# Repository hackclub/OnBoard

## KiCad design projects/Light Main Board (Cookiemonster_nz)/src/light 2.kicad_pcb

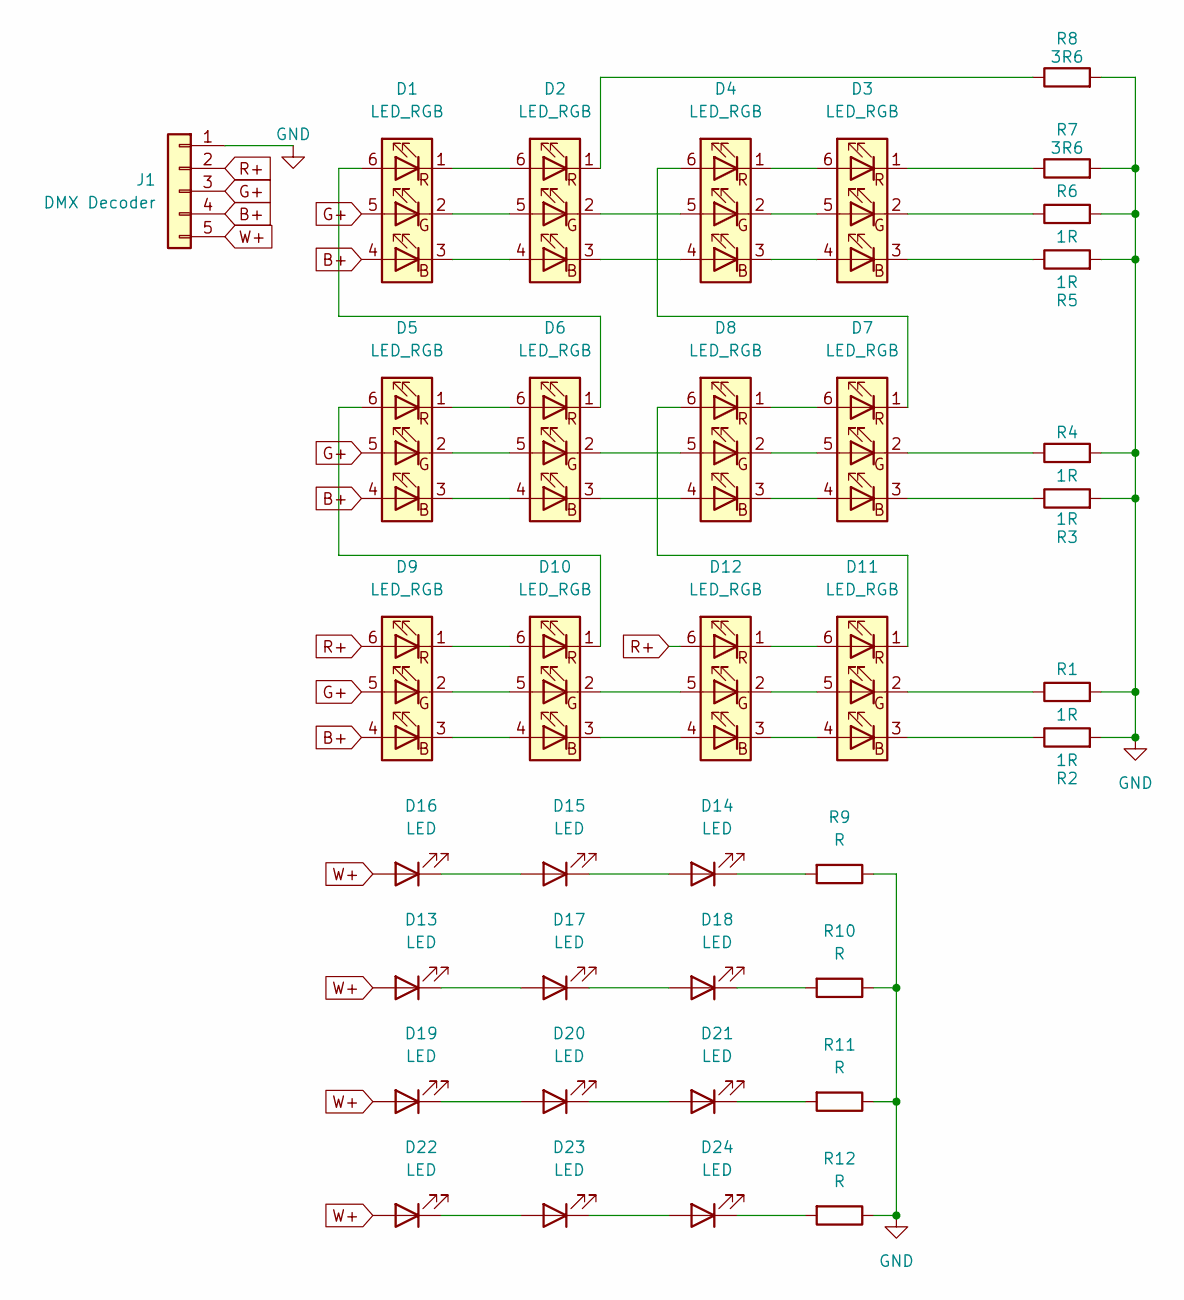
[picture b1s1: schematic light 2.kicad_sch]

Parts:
D1, D2, D3, D4, D5, D6, D7, D8, D9, D10, D11, D12: LED_RGB; RGB LED
D13, D14, D15, D16, D17, D18, D19, D20, D21, D22, D23, D24: LED; White Led Aliexpress ones
J1: DMX Decoder; 5 pin connector
R1, R2, R3, R4, R5, R6: 1R; R_1210_3225Metric
R7, R8: 3R6; R_1210_3225Metric
R9, R10, R11, R12: R; R_1210_3225Metric

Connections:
B+: D1.4 (BA), D5.4 (BA), D9.4 (BA), J1.4 (CH3)
G+: D1.5 (GA), D5.5 (GA), D9.5 (GA), J1.3 (CH2)
GND: J1.1 (COM), R1.2, R2.2, R3.2, R4.2, R5.2, R6.2, R7.2, R8.2, R9.1, R10.1, R11.1, R12.1
unnamed: D1.3 (BK), D2.4 (BA)
unnamed: D1.2 (GK), D2.5 (GA)
unnamed: D1.6 (RA), D6.1 (RK)
unnamed: D1.1 (RK), D2.6 (RA)
unnamed: D2.3 (BK), D4.4 (BA)
unnamed: D2.2 (GK), D4.5 (GA)
unnamed: D2.1 (RK), R8.1
unnamed: D3.4 (BA), D4.3 (BK)
unnamed: D3.3 (BK), R5.1
unnamed: D3.5 (GA), D4.2 (GK)
unnamed: D3.2 (GK), R6.1
unnamed: D3.6 (RA), D4.1 (RK)
unnamed: D3.1 (RK), R7.1
unnamed: D4.6 (RA), D7.1 (RK)
unnamed: D5.3 (BK), D6.4 (BA)
unnamed: D5.2 (GK), D6.5 (GA)
unnamed: D5.1 (RK), D6.6 (RA)
unnamed: D6.3 (BK), D8.4 (BA)
unnamed: D6.2 (GK), D8.5 (GA)
unnamed: D7.4 (BA), D8.3 (BK)
unnamed: D7.3 (BK), R3.1
unnamed: D7.5 (GA), D8.2 (GK)
unnamed: D7.2 (GK), R4.1
unnamed: D7.6 (RA), D8.1 (RK)
unnamed: D9.3 (BK), D10.4 (BA)
unnamed: D10.3 (BK), D12.4 (BA)
unnamed: D9.2 (GK), D10.5 (GA)
unnamed: D10.2 (GK), D12.5 (GA)
unnamed: D9.1 (RK), D10.6 (RA)
unnamed: D5.6 (RA), D10.1 (RK)
unnamed: D11.4 (BA), D12.3 (BK)
unnamed: D11.3 (BK), R2.1
unnamed: D11.5 (GA), D12.2 (GK)
unnamed: D11.2 (GK), R1.1
unnamed: D11.6 (RA), D12.1 (RK)
unnamed: D8.6 (RA), D11.1 (RK)
unnamed: D13.1 (K), D17.2 (A)
unnamed: D14.2 (A), D15.1 (K)
unnamed: D14.1 (K), R9.2
unnamed: D15.2 (A), D16.1 (K)
unnamed: D17.1 (K), D18.2 (A)
unnamed: D18.1 (K), R10.2
unnamed: D19.1 (K), D20.2 (A)
unnamed: D20.1 (K), D21.2 (A)
unnamed: D21.1 (K), R11.2
unnamed: D22.1 (K), D23.2 (A)
unnamed: D23.1 (K), D24.2 (A)
unnamed: D24.1 (K), R12.2
R+: D9.6 (RA), D12.6 (RA), J1.2 (CH1)
W+: D13.2 (A), D16.2 (A), D19.2 (A), D22.2 (A), J1.5 (CH4)

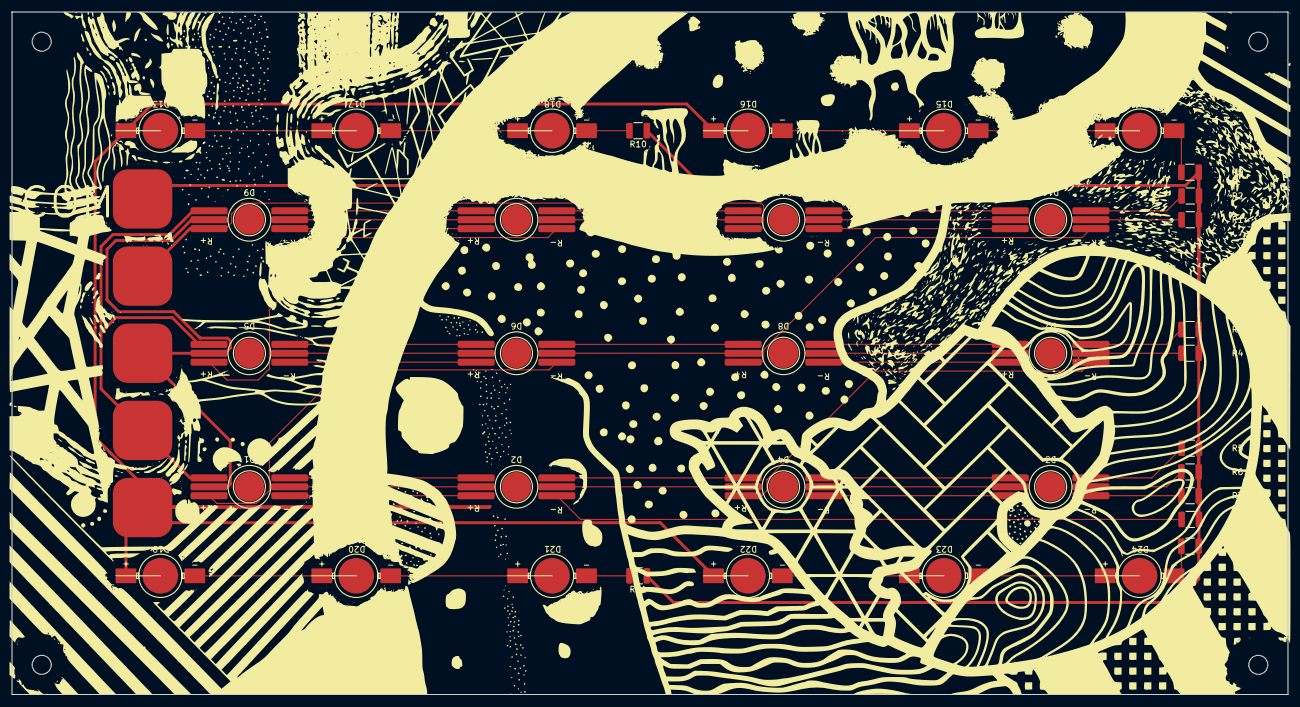
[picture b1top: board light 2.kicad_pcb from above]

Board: 2 copper layers, 215.0 x 115.0 mm, 37 parts (0 on the bottom side), 53 nets.

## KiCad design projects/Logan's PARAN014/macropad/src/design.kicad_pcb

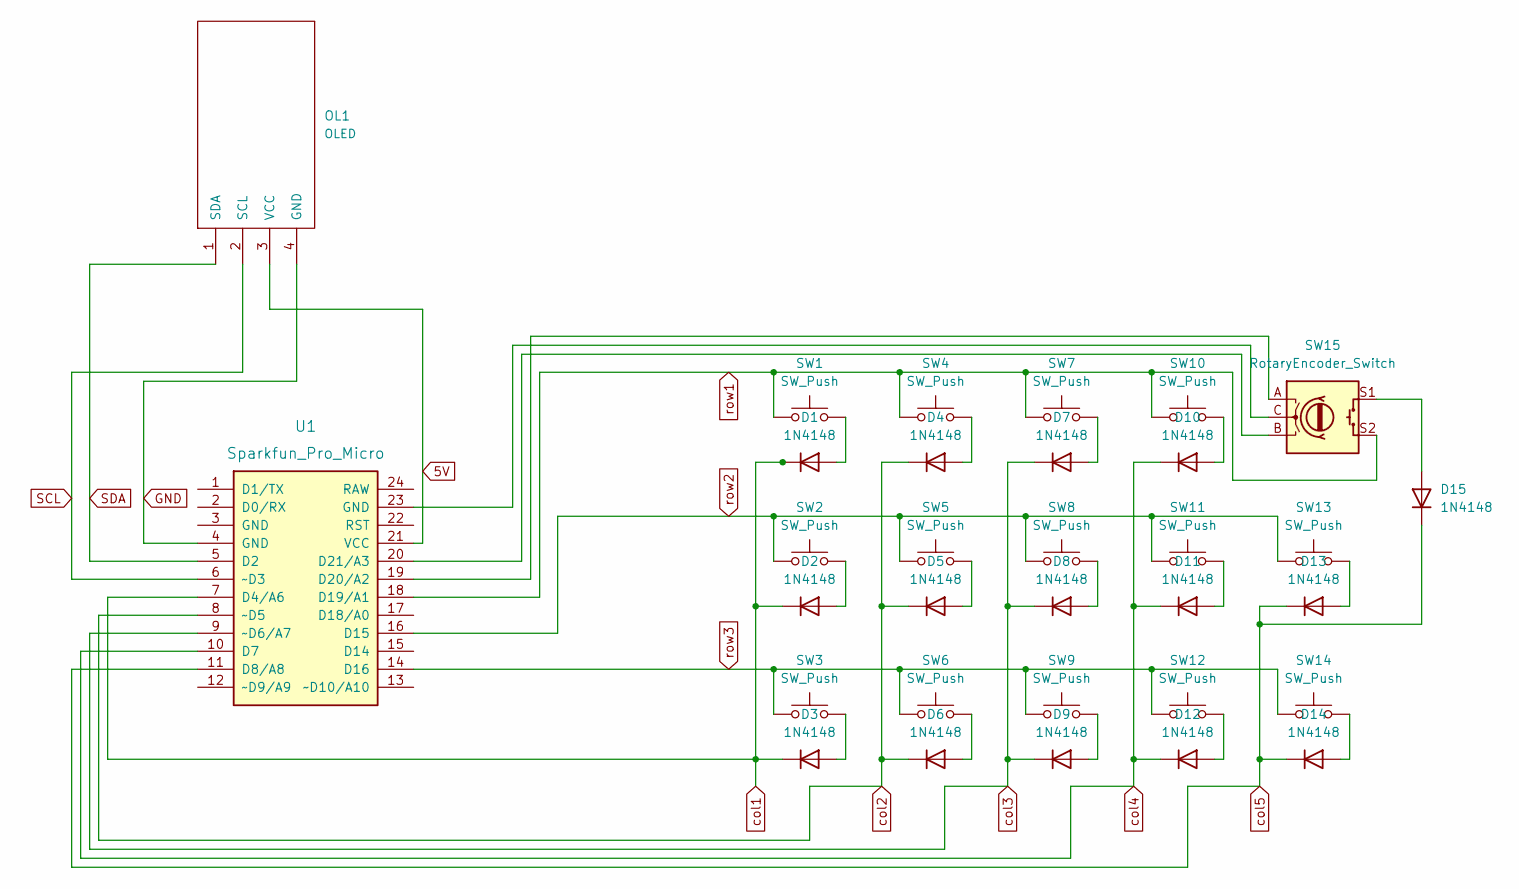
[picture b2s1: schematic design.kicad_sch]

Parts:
D1, D2, D3, D4, D5, D6, D7, D8, D9, D10, D11, D12, D13, D14, D15: 1N4148; D_DO-35_SOD27_P7.62mm_Horizontal
OL1: OLED; OLED_v2
SW1, SW2, SW3, SW4, SW5, SW6, SW7, SW8, SW9, SW10, SW11, SW12, SW13, SW14: SW_Push; SW_Cherry_MX_1.00u_PCB
SW15: RotaryEncoder_Switch; RotaryEncoder_Alps_EC11E-Switch_Vertical_H20mm
U1: Sparkfun_Pro_Micro

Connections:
5V: OL1.3 (VCC), U1.21 (VCC)
GND: OL1.4 (GND), U1.4 (GND)
unnamed: D1.2 (A), SW1.2
unnamed: D2.2 (A), SW2.2
unnamed: D3.2 (A), SW3.2
unnamed: D4.2 (A), SW4.2
unnamed: D5.2 (A), SW5.2
unnamed: D6.2 (A), SW6.2
unnamed: D7.2 (A), SW7.2
unnamed: D8.2 (A), SW8.2
unnamed: D9.2 (A), SW9.2
unnamed: D10.2 (A), SW10.2
unnamed: D11.2 (A), SW11.2
unnamed: D12.2 (A), SW12.2
unnamed: D13.2 (A), SW13.2
unnamed: D14.2 (A), SW14.2
unnamed: D15.2 (A), SW15.S1
unnamed: SW15.A, U1.19 (D20/A2)
unnamed: SW15.B, U1.20 (D21/A3)
unnamed: SW15.C, U1.23 (GND)
SCL: OL1.2 (SCL), U1.6 (~D3)
SDA: OL1.1 (SDA), U1.5 (D2)
col1: D1.1 (K), D2.1 (K), D3.1 (K), U1.7 (D4/A6)
col2: D4.1 (K), D5.1 (K), D6.1 (K), U1.8 (~D5)
col3: D7.1 (K), D8.1 (K), D9.1 (K), U1.9 (~D6/A7)
col4: D10.1 (K), D11.1 (K), D12.1 (K), U1.10 (D7)
col5: D13.1 (K), D14.1 (K), D15.1 (K), U1.11 (D8/A8)
row1: SW1.1, SW4.1, SW7.1, SW10.1, SW15.S2, U1.18 (D19/A1)
row2: SW2.1, SW5.1, SW8.1, SW11.1, SW13.1, U1.16 (D15)
row3: SW3.1, SW6.1, SW9.1, SW12.1, SW14.1, U1.14 (D16)

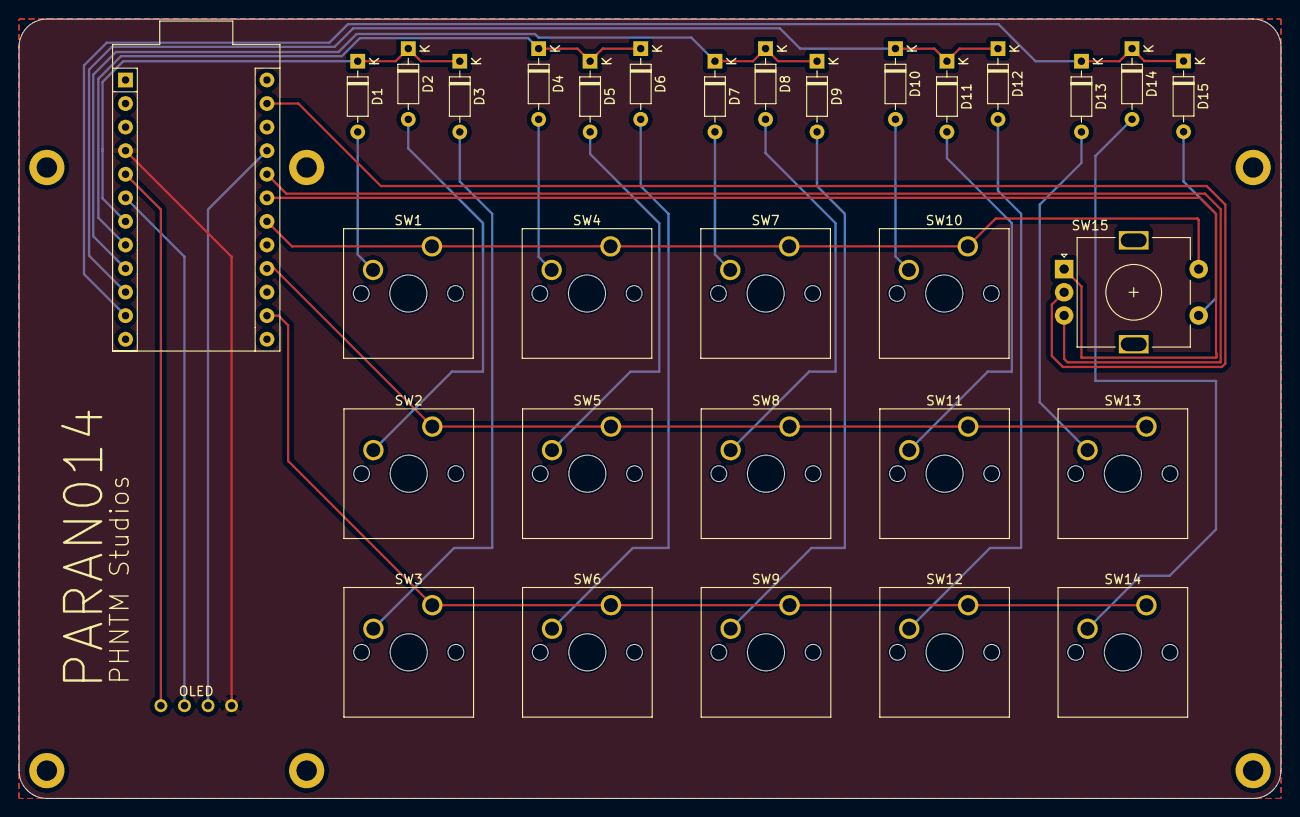
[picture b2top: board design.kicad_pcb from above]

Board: 2 copper layers, 136.0 x 84.0 mm, 32 parts (0 on the bottom side), 30 nets.

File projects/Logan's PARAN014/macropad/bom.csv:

"Id";"Designator";"Footprint";"Quantity";"Designation";"Supplier and ref";
1;"D14,D2,D3,D6,D5,D8,D15,D13,D11,D10,D7,D1,D4,D12,D9";"D_DO-35_SOD27_P7.62mm_Horizontal";15;"1N4148";;;
2;"SW9,SW5,SW3,SW1,SW7,SW13,SW4,SW11,SW10,SW14,SW12,SW6,SW2,SW8";"SW_Cherry_MX_1.00u_PCB";14;"SW_Push";;;
3;"SW15";"RotaryEncoder_Alps_EC11E-Switch_Vertical_H20mm";1;"RotaryEncoder_Switch";;;
4;"U1";"Sparkfun_Pro_Micro";1;"Sparkfun_Pro_Micro";;;
5;"OL1";"OLED_v2";1;"OLED";;;

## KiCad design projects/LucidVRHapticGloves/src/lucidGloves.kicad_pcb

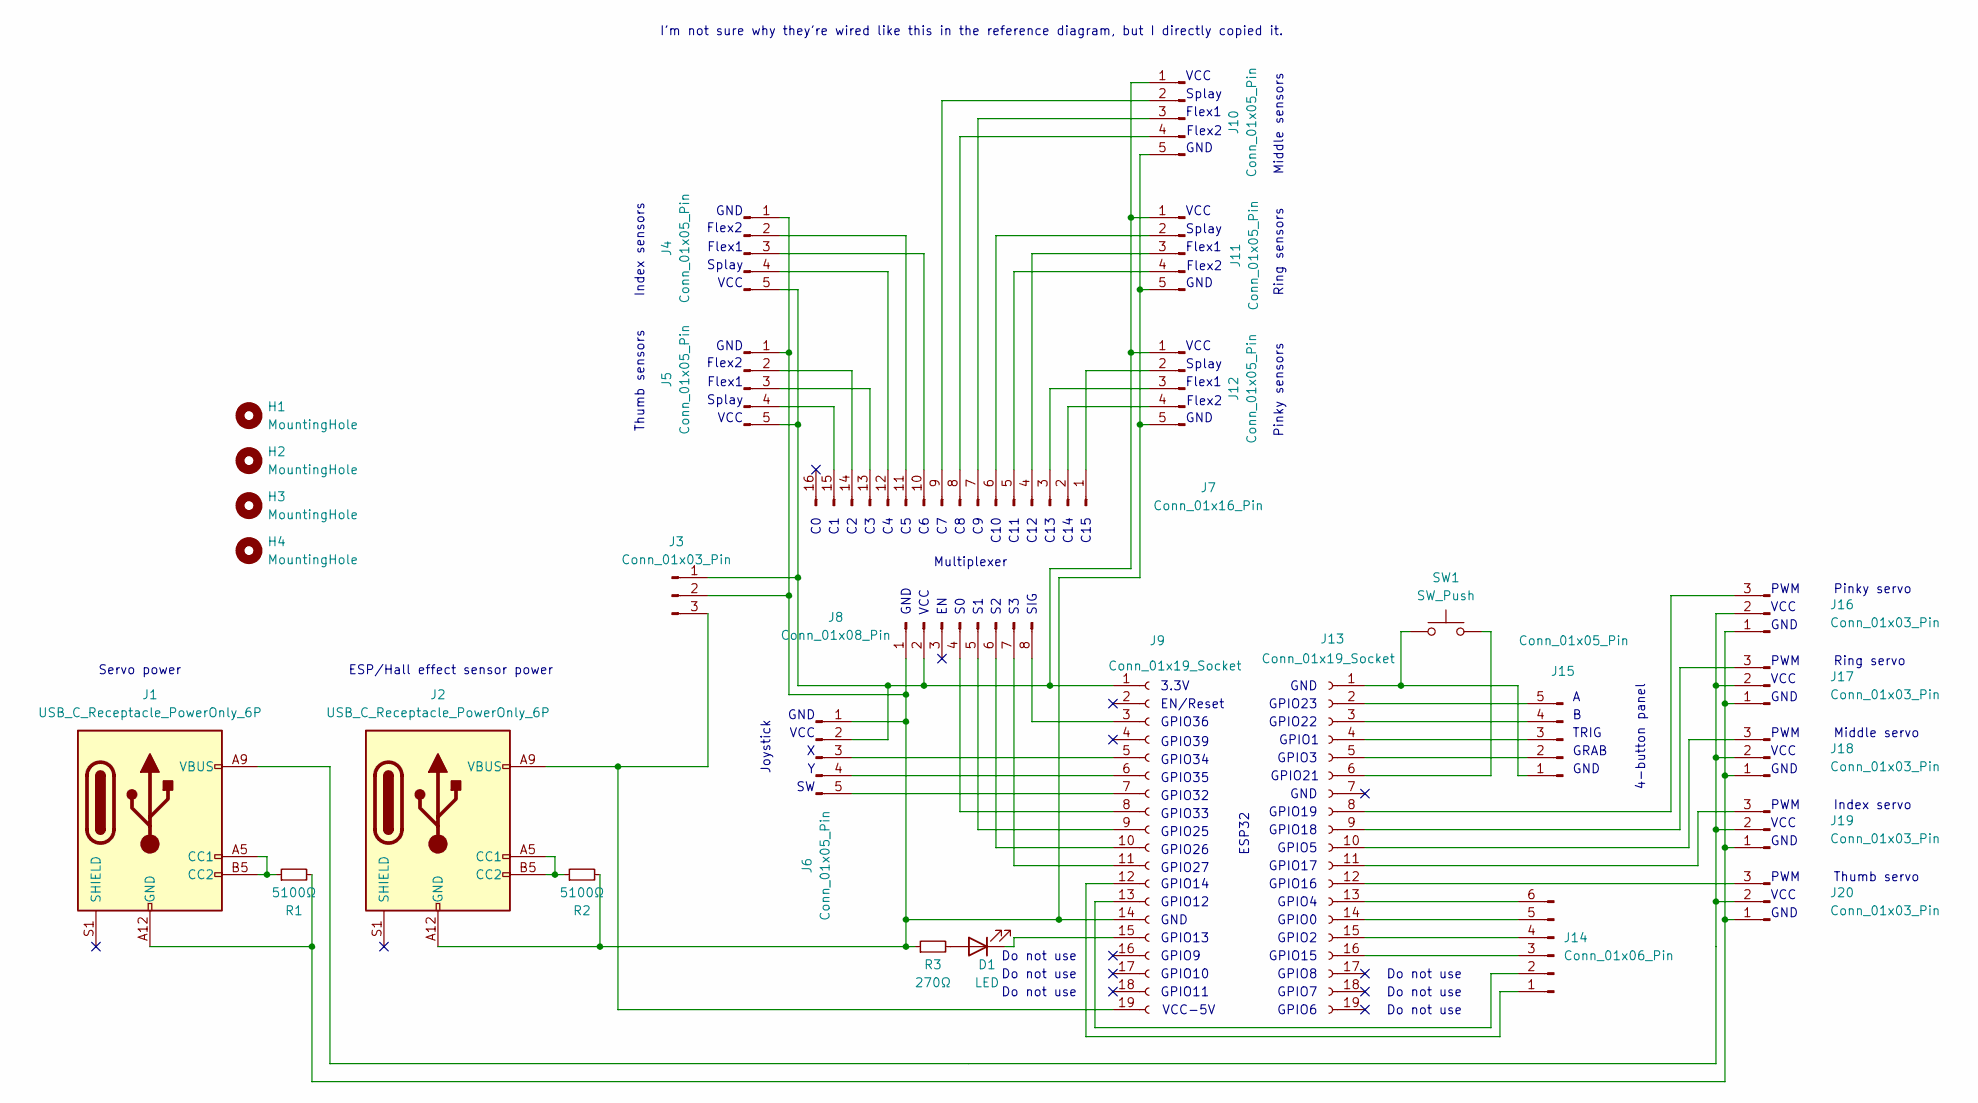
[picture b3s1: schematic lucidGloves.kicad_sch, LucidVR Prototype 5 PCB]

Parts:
D1: LED; LED_PLCC-2_3x2mm_AK; LCSC C2286
H1, H2, H3, H4: MountingHole; MountingHole_3.2mm_M3
J1, J2: USB_C_Receptacle_PowerOnly_6P; USB_C_Receptacle_GCT_USB4135-GF-A_6P_TopMnt_Horizontal; LCSC C2681548
J3: Conn_01x03_Pin; PinHeader_1x03_P2.54mm_Horizontal; LCSC C92159
J4, J5, J10, J11, J12: Conn_01x05_Pin; PinHeader_1x05_P2.54mm_Vertical; LCSC C5156614
J6, J15: Conn_01x05_Pin; PinHeader_1x05_P2.54mm_Horizontal; LCSC C138801
J7: Conn_01x16_Pin; PinHeader_1x16_P2.54mm_Vertical; LCSC C7501270
J8: Conn_01x08_Pin; PinHeader_1x08_P2.54mm_Vertical; LCSC C5156616
J9, J13: Conn_01x19_Socket; PinSocket_1x19_P2.54mm_Vertical; LCSC C319202
J14: Conn_01x06_Pin; PinHeader_1x06_P2.54mm_Horizontal; LCSC C56816
J16, J17, J18, J19, J20: Conn_01x03_Pin; PinHeader_1x03_P2.54mm_Vertical; LCSC C49257
R1, R2: 5100Ω; R_0402_1005Metric; LCSC C103079
R3: 270Ω; R_0402_1005Metric; LCSC C138294
SW1: SW_Push; SW_TH_Tactile_Omron_B3F-10xx; LCSC C271750

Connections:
unnamed: D1.2 (A), R3.2
unnamed: D1.1 (K), J9.15
unnamed: J1.A5 (CC1), J1.B5 (CC2), R1.1
unnamed: J2.A5 (CC1), J2.B5 (CC2), R2.1
unnamed: J2.A9 (VBUS), J2.B9 (VBUS), J3.3, J9.19
unnamed: J4.2, J7.11
unnamed: J4.3, J7.10
unnamed: J4.4, J7.12
unnamed: J5.2, J7.14
unnamed: J5.3, J7.13
unnamed: J5.4, J7.15
unnamed: J6.3, J9.5
unnamed: J6.4, J9.6
unnamed: J6.5, J9.7
unnamed: J8.4, J9.8
unnamed: J8.5, J9.9
unnamed: J8.6, J9.10
unnamed: J8.7, J9.11
unnamed: J8.8, J9.3
unnamed: J3.1, J4.5, J5.5, J6.2, J8.2, J9.1, J10.1, J11.1, J12.1
unnamed: J7.9, J10.2
unnamed: J7.7, J10.3
unnamed: J7.8, J10.4
unnamed: J2.A12 (GND), J2.B12 (GND), J3.2, J4.1, J5.1, J6.1, J8.1, J9.14, J10.5, J11.5, J12.5, R2.2, R3.1
unnamed: J7.6, J11.2
unnamed: J7.4, J11.3
unnamed: J7.5, J11.4
unnamed: J7.1, J12.2
unnamed: J7.3, J12.3
unnamed: J7.2, J12.4
unnamed: J13.1, J15.1, SW1.1
unnamed: J13.2, J15.5
unnamed: J13.3, J15.4
unnamed: J13.4, J15.3
unnamed: J13.5, J15.2
unnamed: J13.6, SW1.2
unnamed: J13.8, J16.3
unnamed: J13.9, J17.3
unnamed: J13.10, J18.3
unnamed: J13.11, J19.3
unnamed: J13.12, J20.3
unnamed: J13.13, J14.6
unnamed: J13.14, J14.5
unnamed: J13.15, J14.4
unnamed: J13.16, J14.3
unnamed: J9.12, J14.1
unnamed: J9.13, J14.2
unnamed: J1.A12 (GND), J1.B12 (GND), J16.1, J17.1, J18.1, J19.1, J20.1, R1.2
unnamed: J1.A9 (VBUS), J1.B9 (VBUS), J16.2, J17.2, J18.2, J19.2, J20.2

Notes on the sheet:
Flex1
GND
C15
SIG
GPIO14
Multiplexer
GPIO4
VCC
GPIO23
GPIO9
Pinky servo
Splay
GPIO39
GPIO34
GPIO35
GPIO26
Do not use
Flex2
GRAB
Index servo
GPIO10
VCC-5V
GPIO3
GPIO15
Servo power
Index sensors
GPIO12
GPIO27
ESP32
GPIO36
GPIO5
C10
GPIO13
GPIO1
GPIO16
GPIO2
C14
PWM
GPIO22
GPIO32

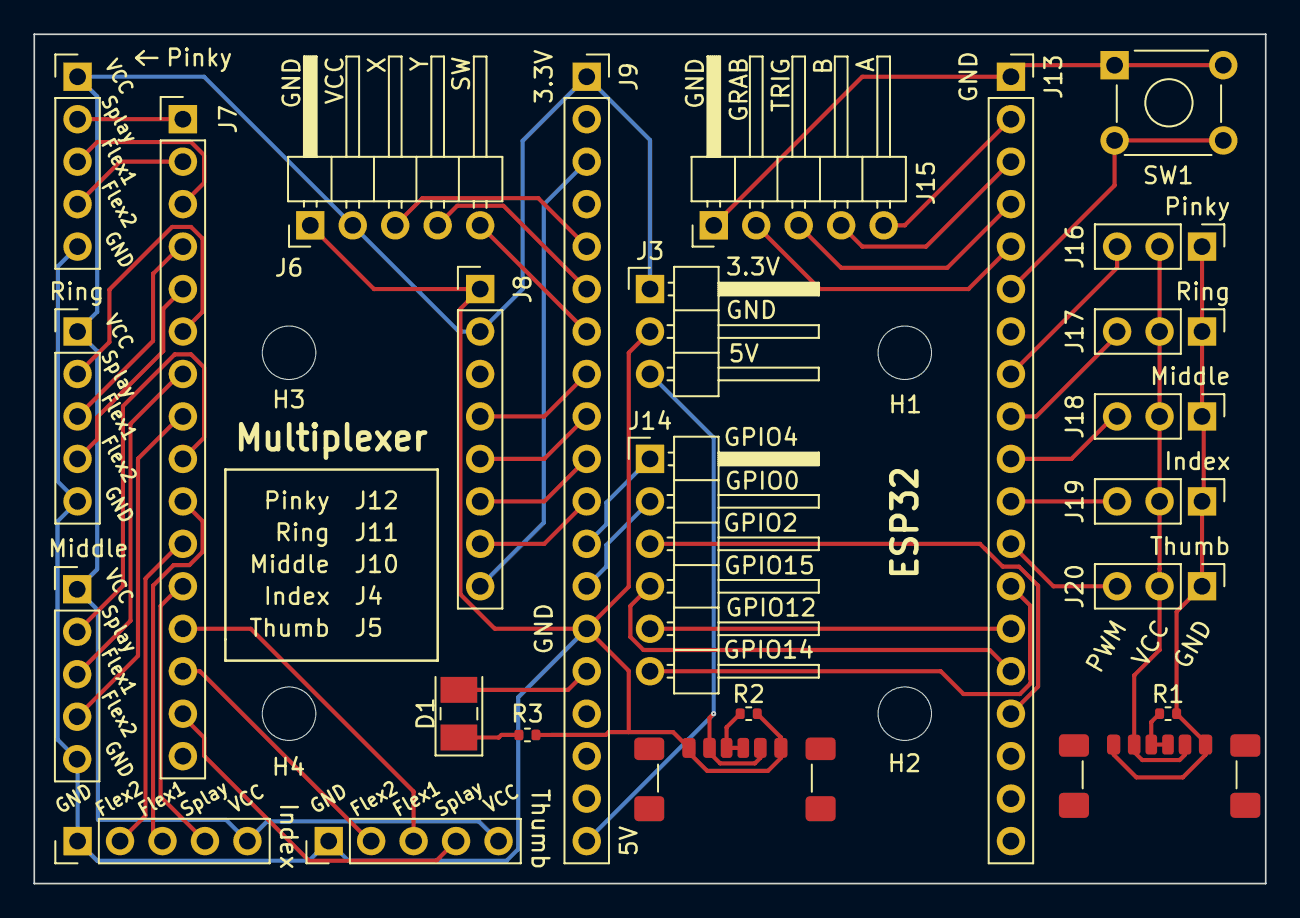
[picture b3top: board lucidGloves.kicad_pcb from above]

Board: 2 copper layers, 73.7 x 50.8 mm, 29 parts (0 on the bottom side), 49 nets.

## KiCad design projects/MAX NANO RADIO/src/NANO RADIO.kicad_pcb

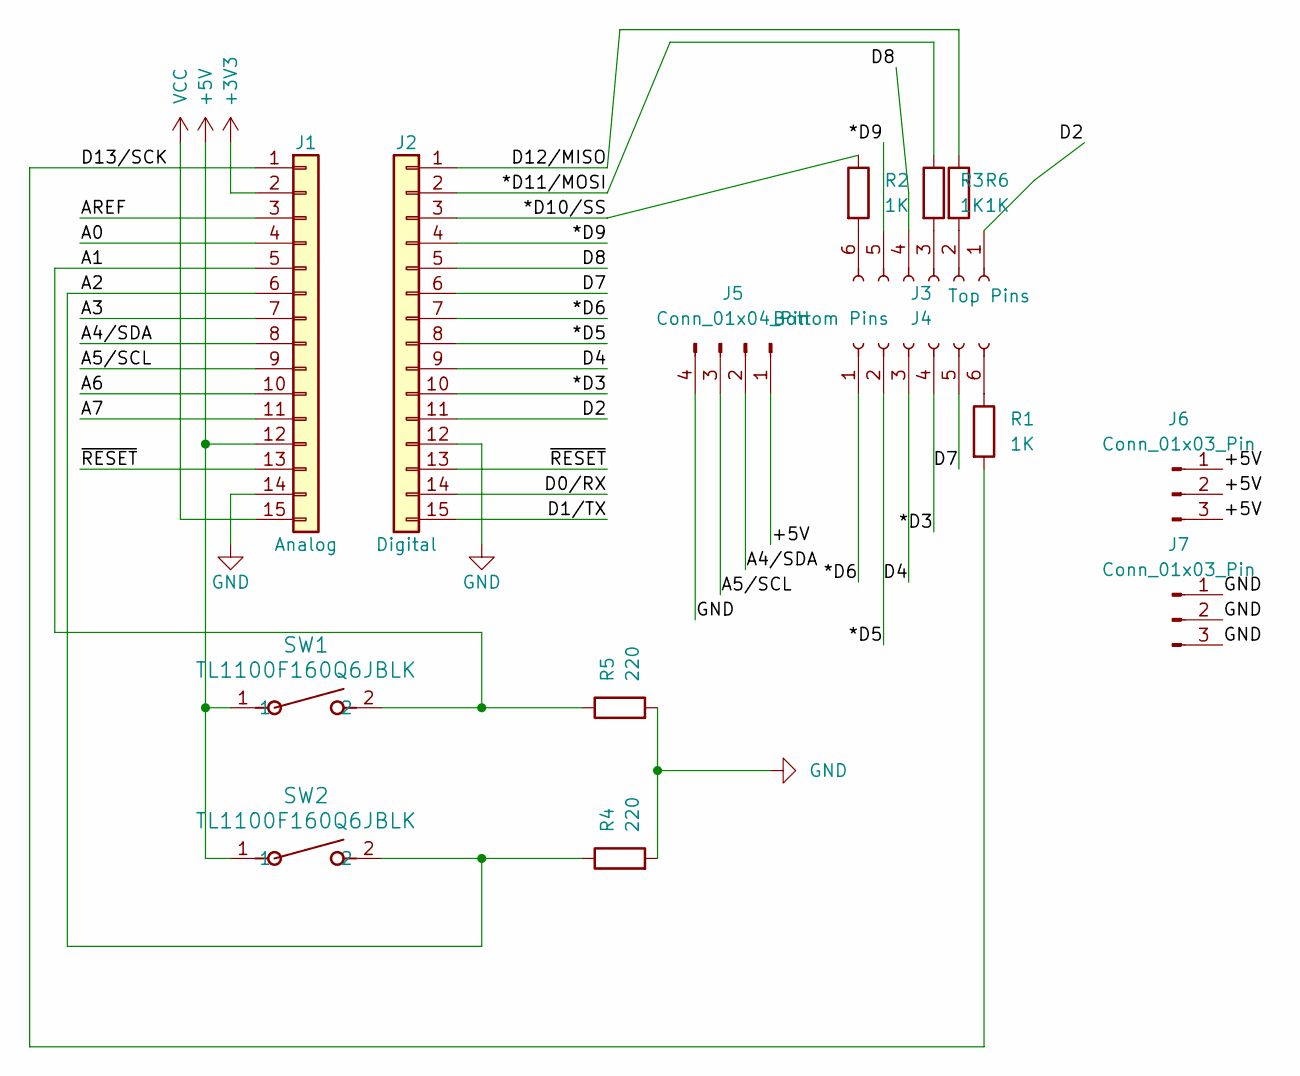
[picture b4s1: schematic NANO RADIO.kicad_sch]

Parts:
J1: Analog; PinHeader_1x15_P2.54mm_Vertical
J2: Digital; PinHeader_1x15_P2.54mm_Vertical
J3: Bottom Pins; PinSocket_1x06_P2.54mm_Vertical
J4: Top Pins; PinSocket_1x06_P2.54mm_Vertical
J5: Conn_01x04_Pin; PinHeader_1x04_P2.54mm_Vertical
J6, J7: Conn_01x03_Pin; PinHeader_1x03_P2.54mm_Vertical
R1, R2, R3, R6: 1K; R_Axial_DIN0207_L6.3mm_D2.5mm_P10.16mm_Horizontal
R4, R5: 220; R_Axial_DIN0207_L6.3mm_D2.5mm_P10.16mm_Horizontal
SW1, SW2: TL1100F160Q6JBLK; CLOCK BUTTON

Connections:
+3V3: J1.2
+5V: J1.12, J5.1, J6.1, J6.2, J6.3, SW1.1, SW2.1
/*D3: J2.10, J3.4
/*D5: J2.8, J3.2
/*D6: J2.7, J3.1
/*D9: J2.4, J4.5
/*D10/SS: J2.3, R2.1
/*D11/MOSI: J2.2, R3.1
/<NO NET>: J1.1, R1.2
/A0: J1.4
/A1: J1.5, R5.1, SW1.2
/A2: J1.6, R4.1, SW2.2
/A3: J1.7
/A4/SDA: J1.8, J5.2
/A5/SCL: J1.9, J5.3
/A6: J1.10
/A7: J1.11
/AREF: J1.3
/D0/RX: J2.14
/D1/TX: J2.15
/D2: J2.11, J4.1
/D4: J2.9, J3.3
/D7: J2.6, J3.5
/D8: J2.5, J4.4
/D12/MISO: J2.1, R6.1
/~RESET: J1.13, J2.13
GND: J1.14, J2.12, J5.4, J7.1, J7.2, J7.3, R4.2, R5.2
unnamed: J3.6, R1.1
unnamed: J4.2, R6.2
unnamed: J4.3, R3.2
unnamed: J4.6, R2.2
VCC: J1.15

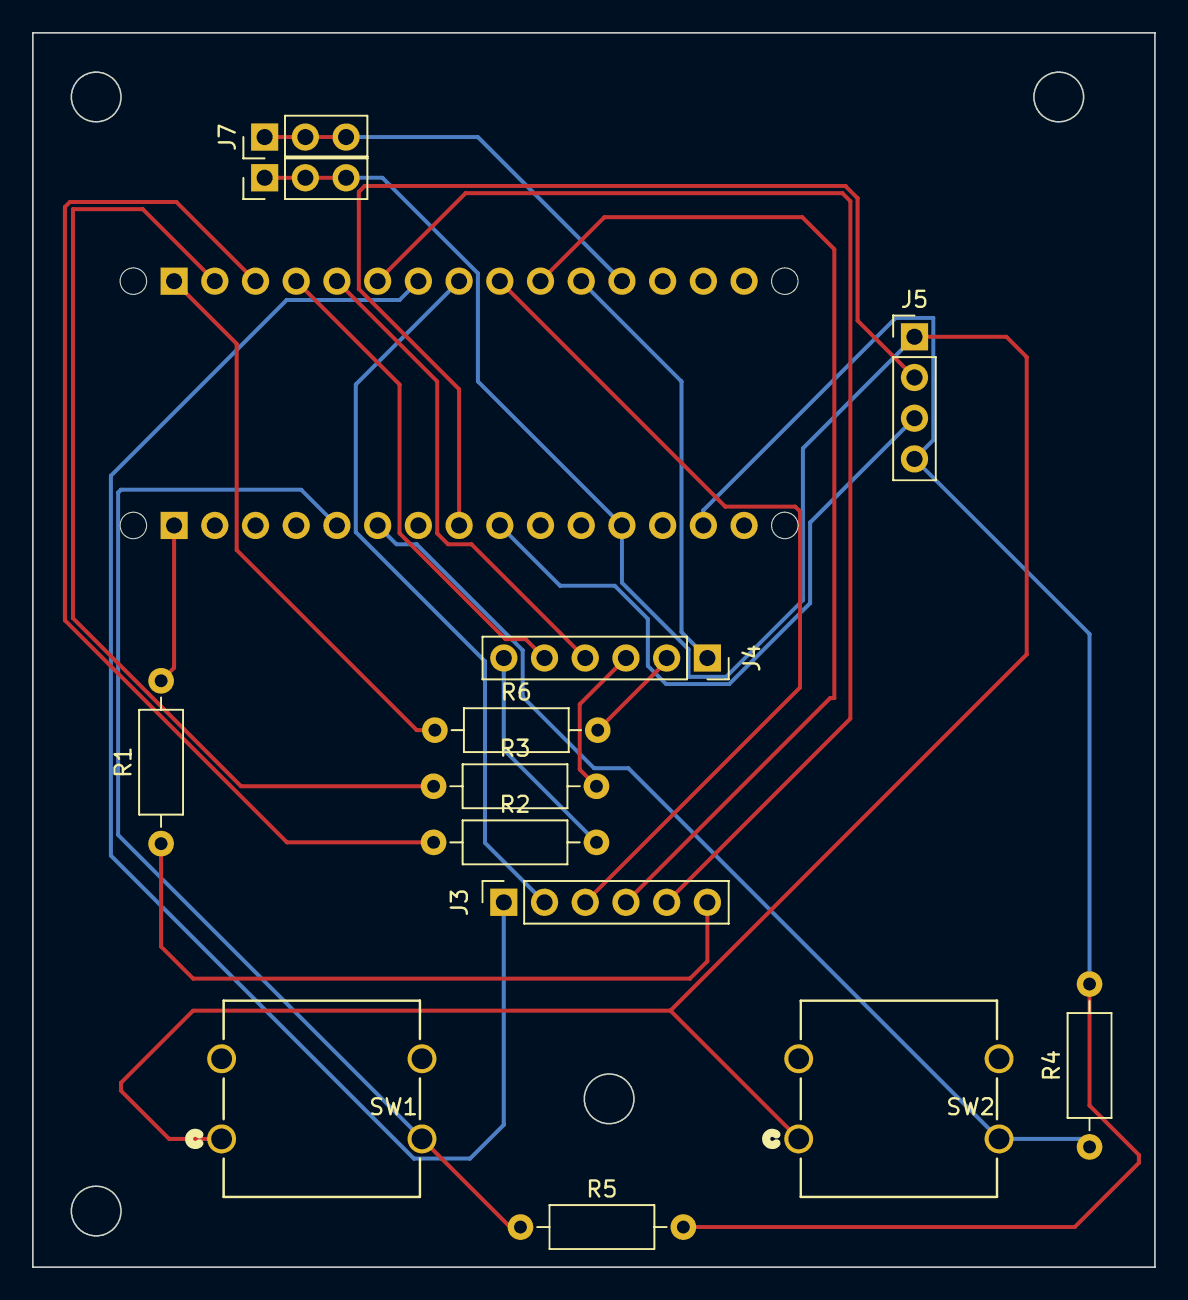
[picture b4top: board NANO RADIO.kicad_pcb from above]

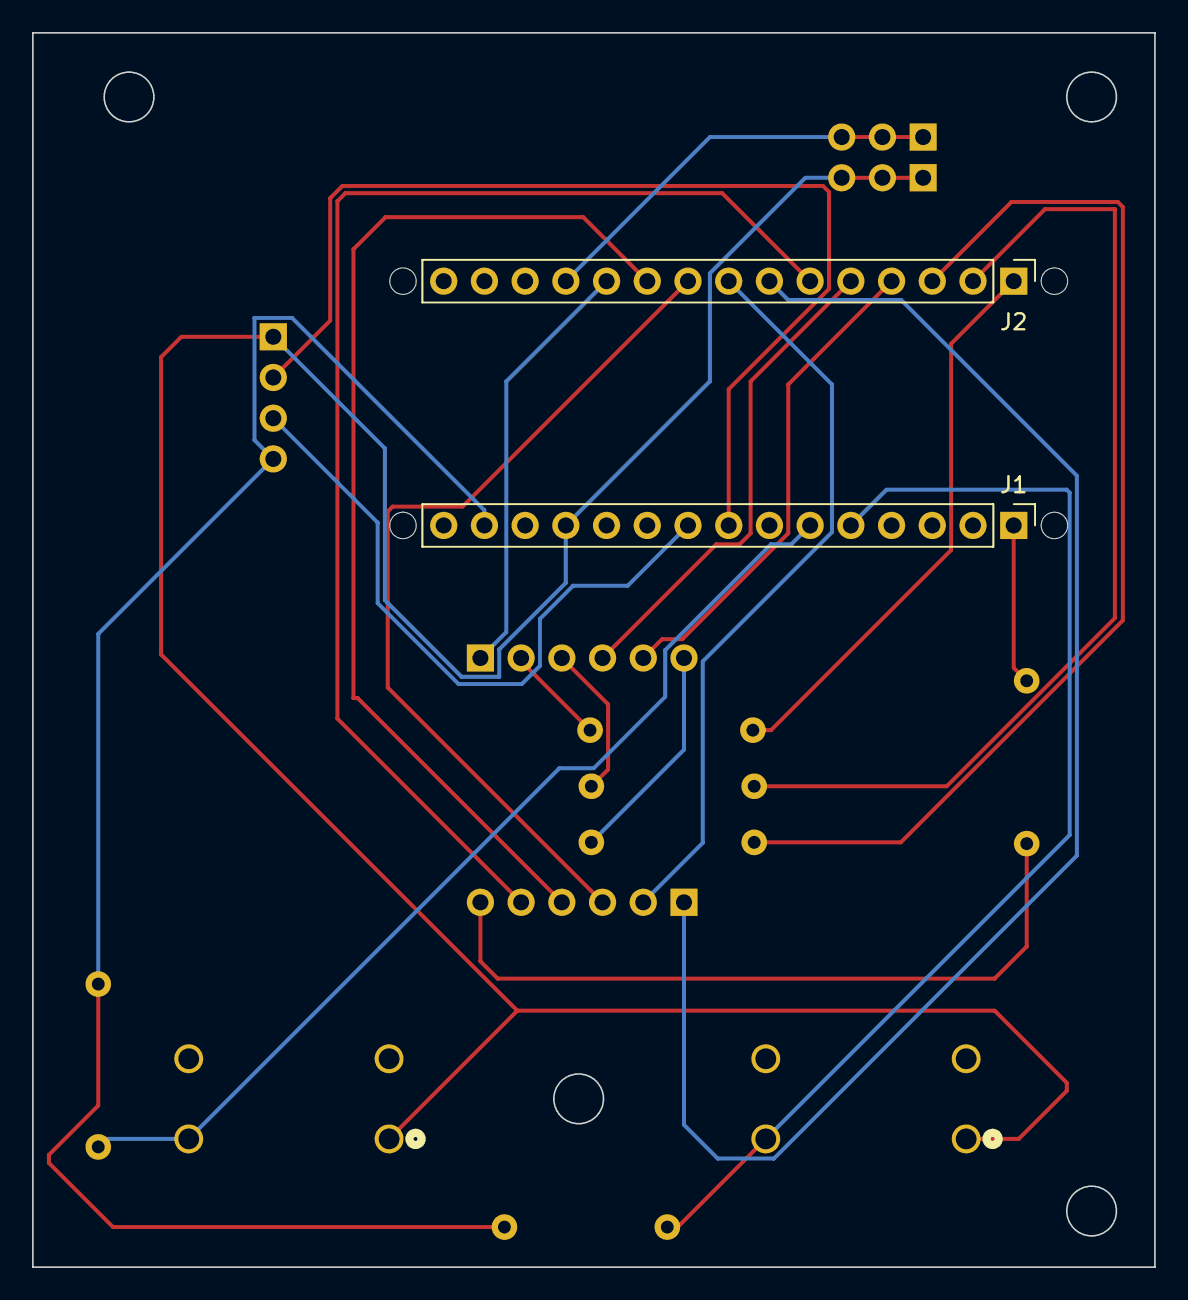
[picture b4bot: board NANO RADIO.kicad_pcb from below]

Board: 2 copper layers, 70.0 x 77.0 mm, 19 parts (2 on the bottom side), 23 nets.

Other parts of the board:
MH1, MH2, MH3, MH4: MountingHole_65mil

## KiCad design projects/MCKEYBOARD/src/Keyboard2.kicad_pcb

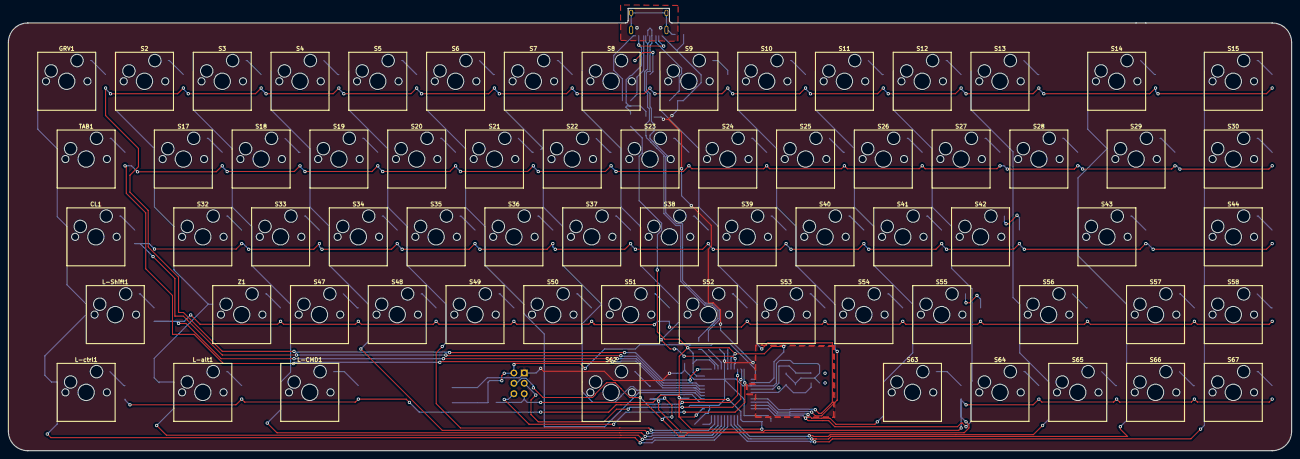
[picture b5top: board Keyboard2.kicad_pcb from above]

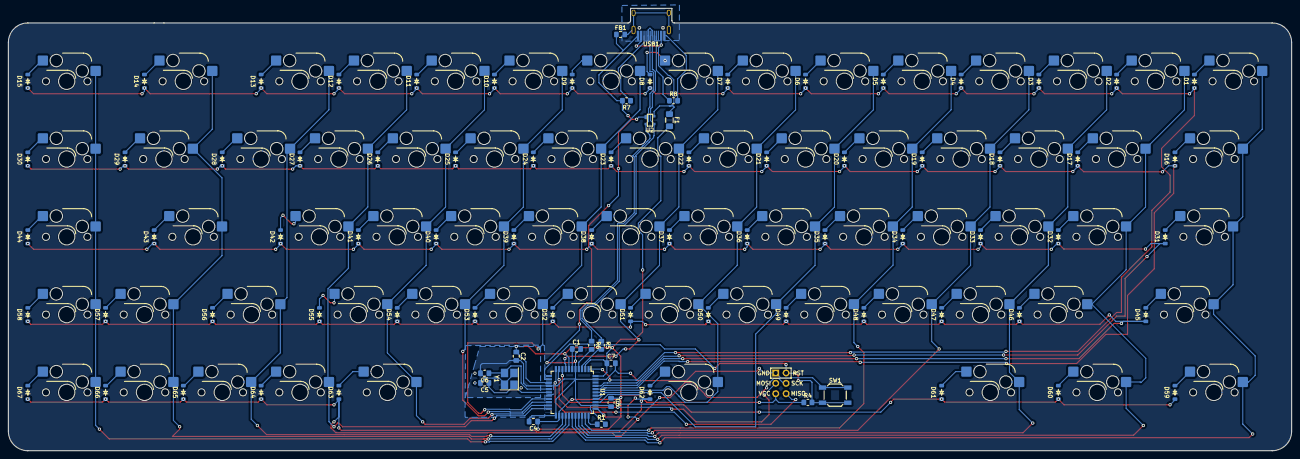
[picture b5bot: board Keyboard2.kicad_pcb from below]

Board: 2 copper layers, 314.3 x 108.3 mm, 155 parts (88 on the bottom side), 105 nets.

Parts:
C1: 1uF; C_0805_2012Metric_Pad1.18x1.45mm_HandSolder
C2, C3, C4: 0.1uF; C_0805_2012Metric_Pad1.18x1.45mm_HandSolder
C5, C6: 22pF; C_0805_2012Metric_Pad1.18x1.45mm_HandSolder
C7: 10uF; C_0805_2012Metric_Pad1.18x1.45mm_HandSolder
CL1: Keyswitch; Hotswap_MX_1.75u
D1, D2, D3, D4, D5, D6, D7, D8, D9, D10, D11, D12, D13, D14, D15, D16, D17, D18, D19, D20, D21, D22, D23, D24, D25, D26, D27, D28, D29, D30, D31, D32, D33, D34, D35, D36, D37, D38, D39, D40, D41, D42, D43, D44, D45, D46, D47, D48, D49, D50, D51, D52, D53, D54, D55, D56, D57, D58, D59, D60, D61, D62, D63, D64, D65, D66, D67: Diode; Diode_SOD-123
F1: 500m; Fuse_1206_3216Metric_Pad1.42x1.75mm_HandSolder
FB1: 60@100MHz; L_0805_2012Metric_Pad1.15x1.40mm_HandSolder
GRV1: Keyswitch; Hotswap_MX_1.00u
J1: AVR-ISP-6; Reset_Pretty-Mask
L-CMD1: Keyswitch; Hotswap_MX_1.25u
L-Shift1: Keyswitch; Hotswap_MX_2.25u
L-alt1: Keyswitch; Hotswap_MX_1.50u
L-ctrl1: Keyswitch; Hotswap_MX_1.50u
R1, R4: 10k; R_0805_2012Metric_Pad1.20x1.40mm_HandSolder
R5, R6: 22; R_0805_2012Metric_Pad1.20x1.40mm_HandSolder
R7, R8: 5.1k; R_0805_2012Metric_Pad1.20x1.40mm_HandSolder
S2, S3, S4, S5, S6, S7, S8, S9, S10, S11, S12, S13, S15, S17, S18, S19, S20, S21, S22, S23, S24, S25, S26, S27, S28, S30, S32, S33, S34, S35, S36, S37, S38, S39, S40, S41, S42, S44, S47, S48, S49, S50, S51, S52, S53, S54, S55, S57, S58, S64, S65, S66, S67: Keyswitch; Hotswap_MX_1.00u
S14: Keyswitch; Hotswap_MX_2.00u
S29: Keyswitch; Hotswap_MX_1.50u
S43: Keyswitch; Hotswap_MX_2.25u
S56: Keyswitch; Hotswap_MX_1.75u
S62: Keyswitch; Hotswap_MX_6.50u
S63: Keyswitch; Hotswap_MX_1.25u
SW1: SW_Push; SW_SPST_SKQG_WithStem
TAB1: Keyswitch; Hotswap_MX_1.50u
U1: ATmega32U4-A; TQFP-44_10x10mm_P0.8mm
U2: PRTR5V0U2X; SOT143B
USB1: HRO-TYPE-C-31-M-12; HRO-TYPE-C-31-M-12-HandSoldering
Y1: 16MHz; Crystal_SMD_3225-4Pin_3.2x2.5mm_HandSoldering
Z1: Keyswitch; Hotswap_MX_1.00u

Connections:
+5V: C2.1, C3.1, C4.1, C7.1, F1.2, J1.2 (VCC), R4.1, U1.2 (UVCC), U1.7 (VBUS), U1.14 (VCC), U1.24 (AVCC), U1.34 (VCC), U1.44 (AVCC)
D+: R6.2, U1.4 (D+)
D-: R5.2, U1.3 (D-)
DN: R5.1, U2.3 (IO2), USB1.5 (DN2), USB1.7 (DN1)
DP: R6.1, U2.2 (IO1), USB1.6 (DP1), USB1.8 (DP2)
Earth: FB1.2, USB1.13 (SHIELD)
GND: C1.2, C2.2, C3.2, C4.2, C5.2, C6.2, C7.2, FB1.1, J1.6 (GND), R1.2, R7.2, R8.2, SW1.1, U1.5 (UGND), U1.15 (GND), U1.23 (GND), U1.35 (GND), U1.43 (GND), U2.1 (GND), USB1.1 (GND), USB1.12 (GND), Y1.2, Y1.4
MISO: J1.1 (MISO), U1.11 (PB3)
MOSI: J1.4 (MOSI), U1.10 (PB2)
unnamed: D1.2 (A), GRV1.2
unnamed: D2.2 (A), S2.2
unnamed: D3.2 (A), S3.2
unnamed: D4.2 (A), S4.2
unnamed: D5.2 (A), S5.2
unnamed: D6.2 (A), S6.2
unnamed: D7.2 (A), S7.2
unnamed: D8.2 (A), S8.2
unnamed: D9.2 (A), S9.2
unnamed: D10.2 (A), S10.2
unnamed: D11.2 (A), S11.2
unnamed: D12.2 (A), S12.2
unnamed: D13.2 (A), S13.2
unnamed: D14.2 (A), S14.2
unnamed: D15.2 (A), S15.2
unnamed: D16.2 (A), TAB1.2
unnamed: D17.2 (A), S17.2
unnamed: D18.2 (A), S18.2
unnamed: D19.2 (A), S19.2
unnamed: D20.2 (A), S20.2
unnamed: D21.2 (A), S21.2
unnamed: D22.2 (A), S22.2
unnamed: D23.2 (A), S23.2
unnamed: D24.2 (A), S24.2
unnamed: D25.2 (A), S25.2
unnamed: D26.2 (A), S26.2
unnamed: D27.2 (A), S27.2
unnamed: D28.2 (A), S28.2
unnamed: D29.2 (A), S29.2
unnamed: D30.2 (A), S30.2
unnamed: CL1.2, D31.2 (A)
unnamed: D32.2 (A), S32.2
unnamed: D33.2 (A), S33.2
unnamed: D34.2 (A), S34.2
unnamed: D35.2 (A), S35.2
unnamed: D36.2 (A), S36.2
unnamed: D37.2 (A), S37.2
unnamed: D38.2 (A), S38.2
unnamed: D39.2 (A), S39.2
unnamed: D40.2 (A), S40.2
unnamed: D41.2 (A), S41.2
unnamed: D42.2 (A), S42.2
unnamed: D43.2 (A), S43.2
unnamed: D44.2 (A), S44.2
unnamed: D45.2 (A), L-Shift1.2
unnamed: D46.2 (A), Z1.2
unnamed: D47.2 (A), S47.2
unnamed: D48.2 (A), S48.2
unnamed: D49.2 (A), S49.2
unnamed: D50.2 (A), S50.2
unnamed: D51.2 (A), S51.2
unnamed: D52.2 (A), S52.2
unnamed: D53.2 (A), S53.2
unnamed: D54.2 (A), S54.2
unnamed: D55.2 (A), S55.2
unnamed: D56.2 (A), S56.2
unnamed: D57.2 (A), S57.2
unnamed: D58.2 (A), S58.2
unnamed: D59.2 (A), L-ctrl1.2
unnamed: D60.2 (A), L-alt1.2
unnamed: D61.2 (A), L-CMD1.2
unnamed: D62.2 (A), S62.2
unnamed: D63.2 (A), S63.2
unnamed: D64.2 (A), S64.2
unnamed: D65.2 (A), S65.2
unnamed: D66.2 (A), S66.2
unnamed: D67.2 (A), S67.2
unnamed: C1.1, U1.6 (UCAP)
unnamed: C5.1, U1.17 (XTAL1), Y1.1
unnamed: C6.1, U1.16 (XTAL2), Y1.3
unnamed: R1.1, U1.33 (~HWB/PE2)
unnamed: R8.1, USB1.4 (CC1)
unnamed: R7.1, USB1.10 (CC2)
RESET: J1.5 (~RST), R4.2, SW1.2, U1.13 (~RESET)
SCK: J1.3 (SCK), U1.9 (PB1)
VCC: F1.1, U2.4 (VCC), USB1.2 (VBUS), USB1.11 (VBUS)
col0: CL1.1, GRV1.1, L-Shift1.1, L-ctrl1.1, TAB1.1, U1.28 (PB4)
col1: L-alt1.1, S2.1, S17.1, S32.1, U1.29 (PB5), Z1.1
col2: L-CMD1.1, S3.1, S18.1, S33.1, S47.1, U1.30 (PB6)
col3: S4.1, S19.1, S34.1, S48.1, U1.31 (PC6)
col4: S5.1, S20.1, S35.1, S49.1, U1.32 (PC7)
col5: S6.1, S21.1, S36.1, S50.1, U1.37 (PF6)
col6: S7.1, S22.1, S37.1, S51.1, S62.1, U1.38 (PF5)
col7: S8.1, S23.1, S38.1, S52.1, U1.8 (PB0)
col8: S9.1, S24.1, S39.1, S53.1, U1.19 (PD1)
col9: S10.1, S25.1, S40.1, S54.1, U1.20 (PD2)
col10: S11.1, S26.1, S41.1, S55.1, S63.1, U1.21 (PD3)
col11: S12.1, S27.1, S42.1, S64.1, U1.22 (PD5)
col12: S13.1, S28.1, S56.1, S65.1, U1.25 (PD4)
col13: S14.1, S29.1, S43.1, S57.1, S66.1, U1.26 (PD6)
col14: S15.1, S30.1, S44.1, S58.1, S67.1, U1.27 (PD7)
row0: D1.1 (K), D2.1 (K), D3.1 (K), D4.1 (K), D5.1 (K), D6.1 (K), D7.1 (K), D8.1 (K), D9.1 (K), D10.1 (K), D11.1 (K), D12.1 (K), D13.1 (K), D14.1 (K), D15.1 (K), U1.1 (PE6)
row1: D16.1 (K), D17.1 (K), D18.1 (K), D19.1 (K), D20.1 (K), D21.1 (K), D22.1 (K), D23.1 (K), D24.1 (K), D25.1 (K), D26.1 (K), D27.1 (K), D28.1 (K), D29.1 (K), D30.1 (K), U1.39 (PF4)
row2: D31.1 (K), D32.1 (K), D33.1 (K), D34.1 (K), D35.1 (K), D36.1 (K), D37.1 (K), D38.1 (K), D39.1 (K), D40.1 (K), D41.1 (K), D42.1 (K), D43.1 (K), D44.1 (K), U1.41 (PF0)
row3: D45.1 (K), D46.1 (K), D47.1 (K), D48.1 (K), D49.1 (K), D50.1 (K), D51.1 (K), D52.1 (K), D53.1 (K), D54.1 (K), D55.1 (K), D56.1 (K), D57.1 (K), D58.1 (K), U1.40 (PF1)
row4: D59.1 (K), D60.1 (K), D61.1 (K), D62.1 (K), D63.1 (K), D64.1 (K), D65.1 (K), D66.1 (K), D67.1 (K), U1.36 (PF7)
